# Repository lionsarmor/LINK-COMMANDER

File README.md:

# LINK COMMANDER — Rev D

**Buy the breadboard parts:** [Amazon checklist + ASINs](SHOPPING-AMAZON.md) · [Mouser checklist + SKUs](SHOPPING-MOUSER.md) · [Amazon order CSV](SHOPPING-AMAZON-ORDER.csv) · [Full Mouser CSV](SHOPPING-MOUSER-ORDER.csv) · [Keyboard-only Mouser CSV](SHOPPING-MOUSER-KEYBOARD.csv). Choose one checklist; do not buy both. Each covers the build and explicitly identifies outside-store exceptions. Skip parts already owned.

**Five finished PCB builds:** [Full Mouser PO (PDF)](MOUSER-PO-01-FIVE-PCBS.pdf) · [Full PO CSV](MOUSER-PO-01-FIVE-PCBS.csv) · [Chips-only PO (PDF)](MOUSER-PO-02-CHIPS-ONLY.pdf) · [Chips-only CSV](MOUSER-PO-02-CHIPS-ONLY.csv). Plain supplier parts tables; not submitted. Full order needs five modules and five fabricated PCBs supplied separately.

A through-hole USB keyboard and mouse adapter for the **Commander X16**.
The RP2040-Zero translates supported wired devices or 2.4 GHz USB receivers
into PS/2 keyboard and mouse signals. Rev D removes all gamepad support.

**Two USB inputs. Two PCB-mounted 7-pin DIN outputs. Two socketed DIP chips.**
The RP2040-Zero plugs into removable headers; every other carrier part is
through-hole. No USB hub or onboard radio is required.

A separate regulated **5 V / 2 A supply** powers the module and USB ports.
The X16 PS/2 +5 V lines supply only their signal pull-ups.

**Start breadboarding:** [Wiring instructions and parts list](BREADBOARD.md) ·
[Parts CSV](BREADBOARD-PARTS.csv) · [Complete wiring CSV](BREADBOARD-WIRING.csv)

- [Exploratory PS/2 simulation and its limits](hardware/rev-d/simulation/README.md)
- [Test points and expected readings](hardware/rev-d/test-points.md)
- [Student guide: how it works](hardware/rev-d/student-guide.md)
- [One-page schematic PDF](hardware/rev-d/review/schematic.pdf)
- [Assembly PDF](hardware/rev-d/review/assembly.pdf)
- [Editable KiCad project](hardware/rev-d/kicad/link-commander.kicad_pro)
- [Complete Rev D review ZIP](hardware/link-commander-rev-d-review.zip)
- [Breadboard guide and custom cables](BREADBOARD.md)
- [Pin-by-pin wiring table](hardware/rev-d/breadboard-wiring.csv)
- [Grouped BOM](hardware/rev-d/bom-grouped.csv) and [purchasing notes](hardware/rev-d/parts.md)
- [Design details and validation status](hardware/rev-d/README.md)
- [Firmware requirements](hardware/rev-d/firmware-contract.md)

The rounded **140 × 80 mm, two-layer PCB** retains 50 electrical parts
and four mounting holes, and now adds **26 labeled through-hole test pads**.
The student schematic shows seven circuit sections plus a test-point section,
physical pin numbers and connected wires.

**Engineering prototype:** CAD checks pass, but firmware, physical fit,
receiver compatibility and electrical operation still require testing.
No working bridge firmware or fabrication release is included yet. Start
with the standalone keyboard breadboard before connecting the X16.

Rev D uses **non-inverted PS/2 sense signals** and new component reference
numbers. Use only its wiring tables. Remove JP1 before connecting the
module's USB-C to a computer.

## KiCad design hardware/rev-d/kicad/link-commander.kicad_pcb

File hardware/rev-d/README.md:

# LINK COMMANDER — Rev D

Rev D translates supported **USB keyboards and mice** into the PS/2
keyboard and mouse interfaces used by the Commander X16. Wired peripherals
and manufacturers' 2.4 GHz USB receivers use the same two USB input ports.
Gamepad support has been removed from this revision.

The RP2040-Zero plugs into removable headers. Every other carrier component
is through-hole. There are **two socketed DIP chips and four transistors**.
The board is **140 × 80 mm**, has **two copper layers** and 4 mm corner radii,
and retains the KiCad/open-hardware logos.

The board and USB receivers use a separate regulated **5 V / 2 A supply**.
The X16 PS/2 +5 V pins supply only their signal pull-ups; they do not power
the RP2040 or USB ports. All grounds are shared.

## Start here

- [Exploratory PS/2 simulation and its limits](simulation/README.md)
- [Test-point map and expected readings](test-points.md) and [probe CSV](test-points.csv)
- [Student design guide: how the circuit works](student-guide.md)
- [One-page schematic PDF](review/schematic.pdf)
- [Assembly PDF](review/assembly.pdf) and [PCB preview](review/pcb-top.png)
- [Editable KiCad project](kicad/link-commander.kicad_pro)
- [Breadboard guide and custom cable table](breadboard.md)
- [Every physical pin](breadboard-wiring.csv) and [connections grouped by net](net-connections.csv)
- [Grouped BOM](bom-grouped.csv), [individual BOM](bom.csv), [purchasing notes](parts.md)
- [Firmware interface and test requirements](firmware-contract.md)
- [Validation reports](review/design-checks.txt), [PCB DRC](review/pcb-drc.txt)
- [Rebuild instructions](tools/README.md)

## What changed from Rev C

| | Rev C | Rev D |
|---|---:|---:|
| USB inputs | 4 | 2: keyboard and mouse |
| DIN outputs | 4 | 2: PS/2 keyboard and mouse |
| Socketed DIP ICs | 17 | 2 |
| Transistors | 7 | 4 |
| Circuit parts plus mounting holes | 143 | 54 |
| Additional bare test holes | — | 26 |
| Board | 230 × 130 mm, four layers | 140 × 80 mm, two layers |

The gamepad shift registers, resistor networks and control gates are gone.
One TPS2042P replaces the two individual USB power chips. One CD4050 handles all four PS/2 sense lines. The separate HC14 inverter
stage and four input/output series-resistor pairs have been removed. Both
channels of the USB power chip are enabled directly by ground, so no shared enable
transistor or RUN_ENABLE GPIO is required. Port fault LEDs remain useful
for students during bring-up.

**Rev D sense signals are non-inverting:** HIGH means the cable line is
HIGH. The old Rev C firmware assumptions and component reference numbers
must not be reused without updating them. PS/2 drive HIGH still pulls LOW.

The DIN-to-PS/2 cable signal assignment is unchanged, but the output
connectors are now J4 and J5. Use the Rev D wiring tables exclusively.

## Test access

TP1–TP26 add 26 bare plated holes: eight power rails, twelve PS/2
drive/cable/sense nodes, two USB fault outputs and four grounds. The board
now has 80 CAD positions: 50 electrical parts, four mounting holes and
26 optional test contacts. It still needs only two socketed chips.
USB data probing uses existing resistor pads to avoid added test branches.

## Prototype status

The saved PCB passes KiCad clearance/connectivity checks, and the exported
schematic netlist matches the canonical circuit. All populated component
pads are through-hole. These are CAD checks, not evidence of a working
physical adapter: module/socket fit, USB signal integrity, power sequencing,
PS/2 timing, firmware and receiver compatibility still need bench testing.
The two-layer ground pour is interrupted by routes; it is not a dedicated
unbroken reference plane or a controlled-impedance qualification.

No working bridge firmware or fabrication release is supplied here. Start
with the standalone breadboard tests. Do not connect the X16 until the
firmware and cable checks in the guide have passed.

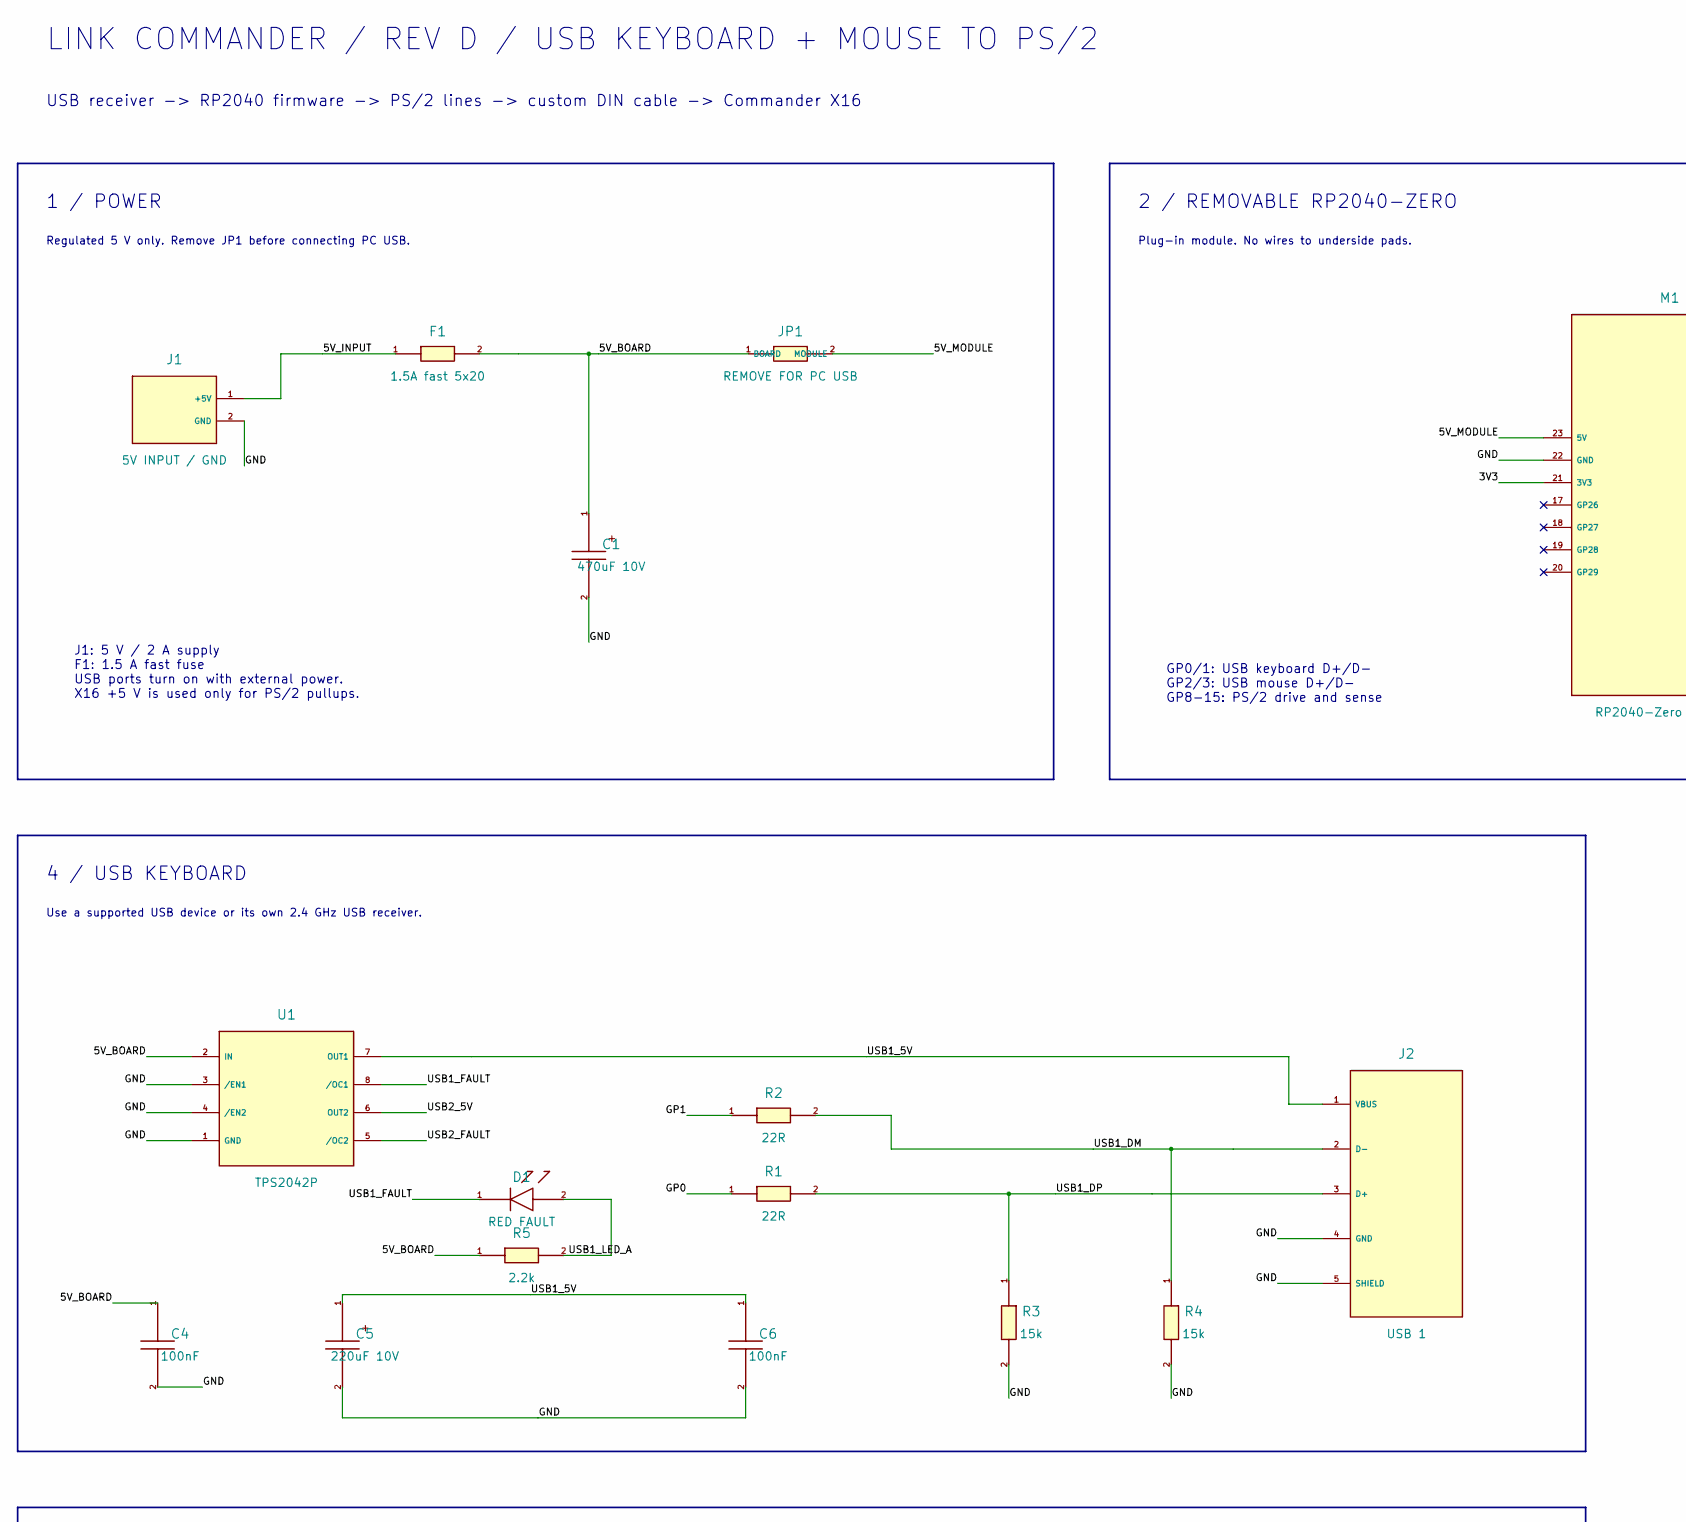
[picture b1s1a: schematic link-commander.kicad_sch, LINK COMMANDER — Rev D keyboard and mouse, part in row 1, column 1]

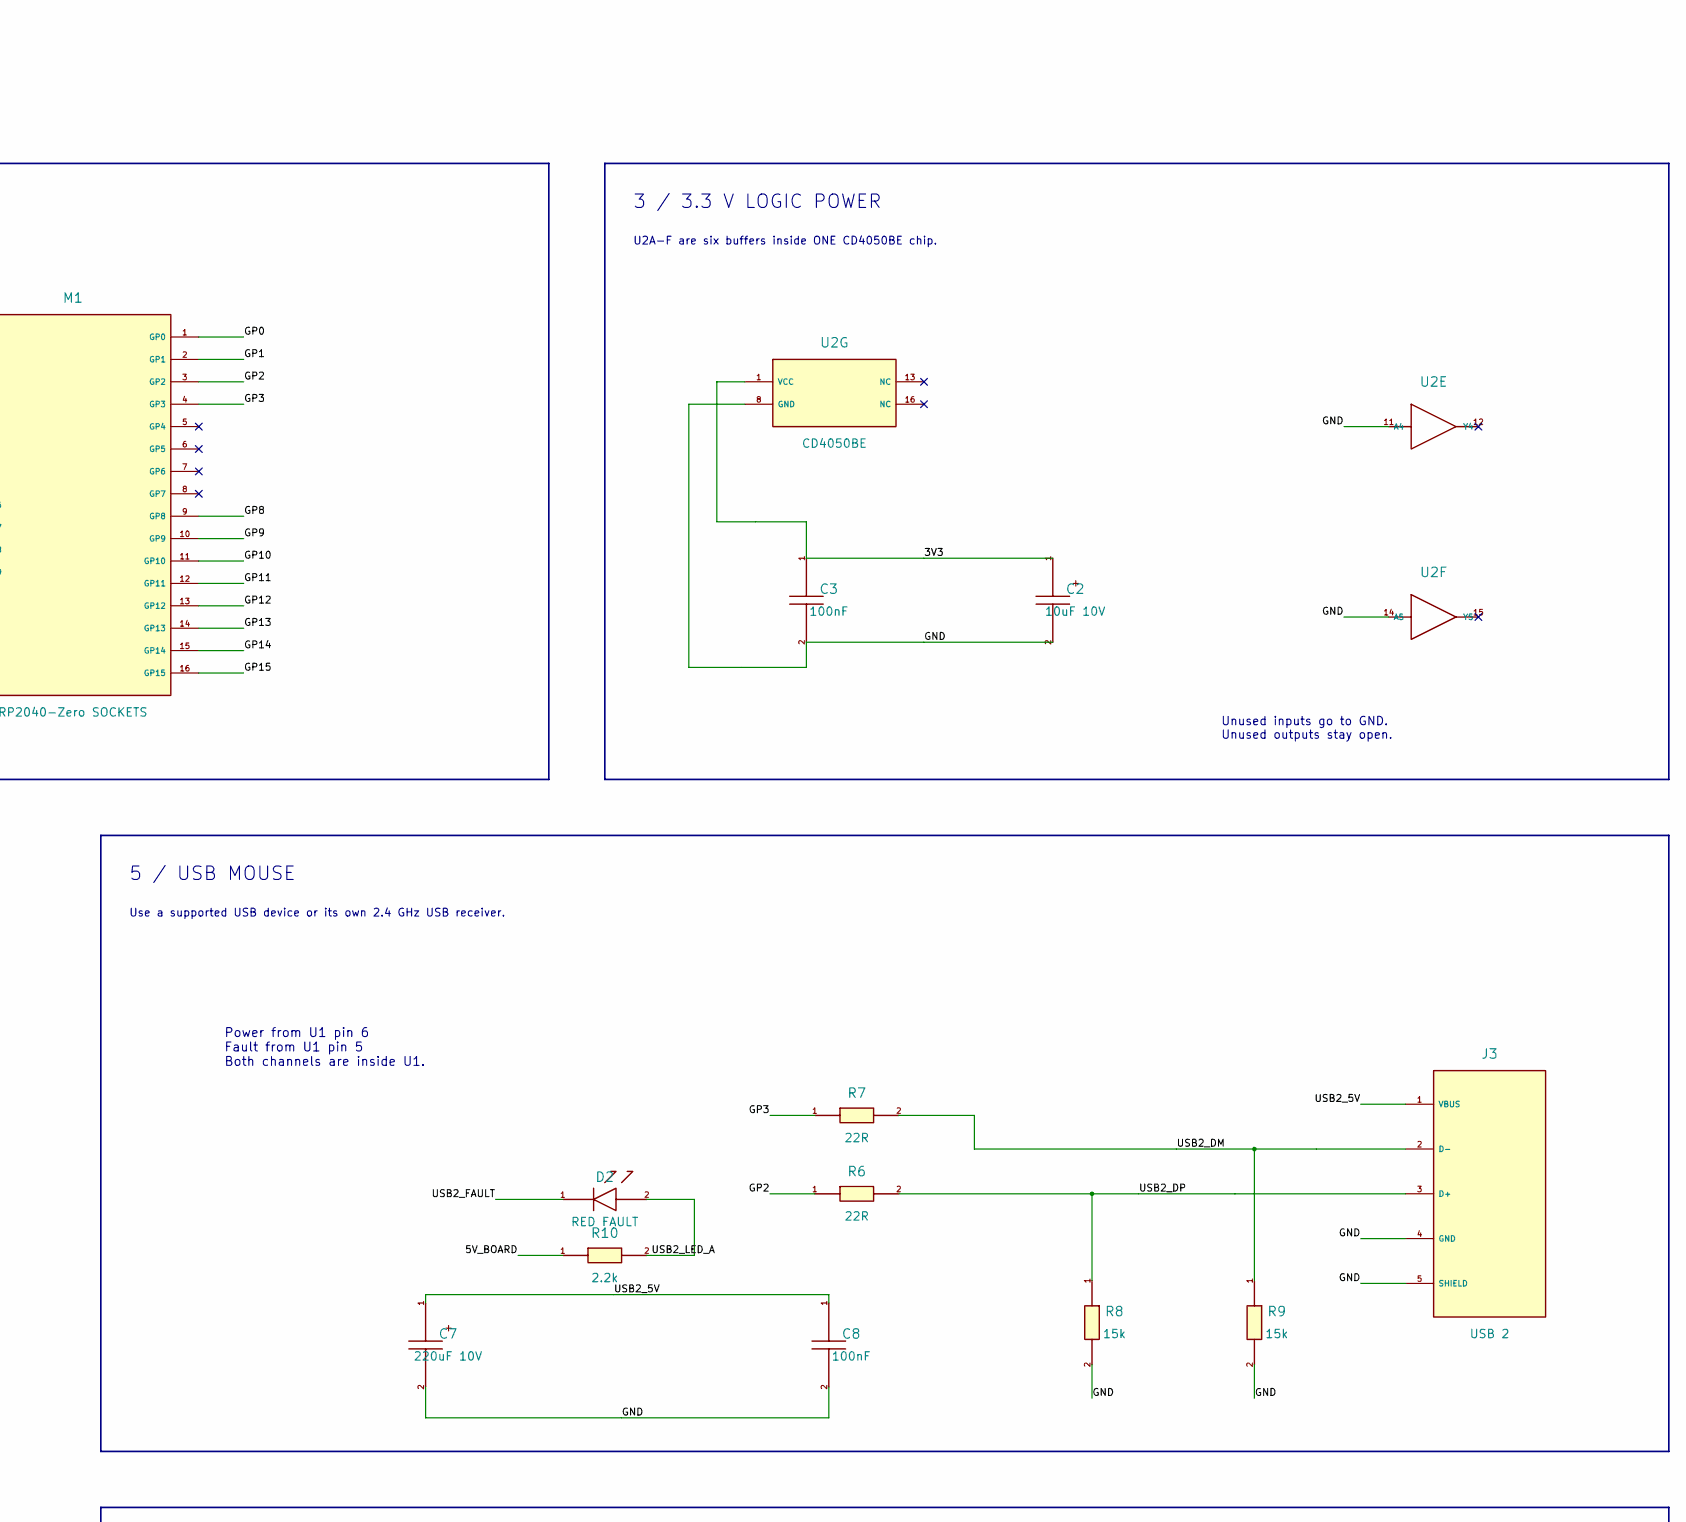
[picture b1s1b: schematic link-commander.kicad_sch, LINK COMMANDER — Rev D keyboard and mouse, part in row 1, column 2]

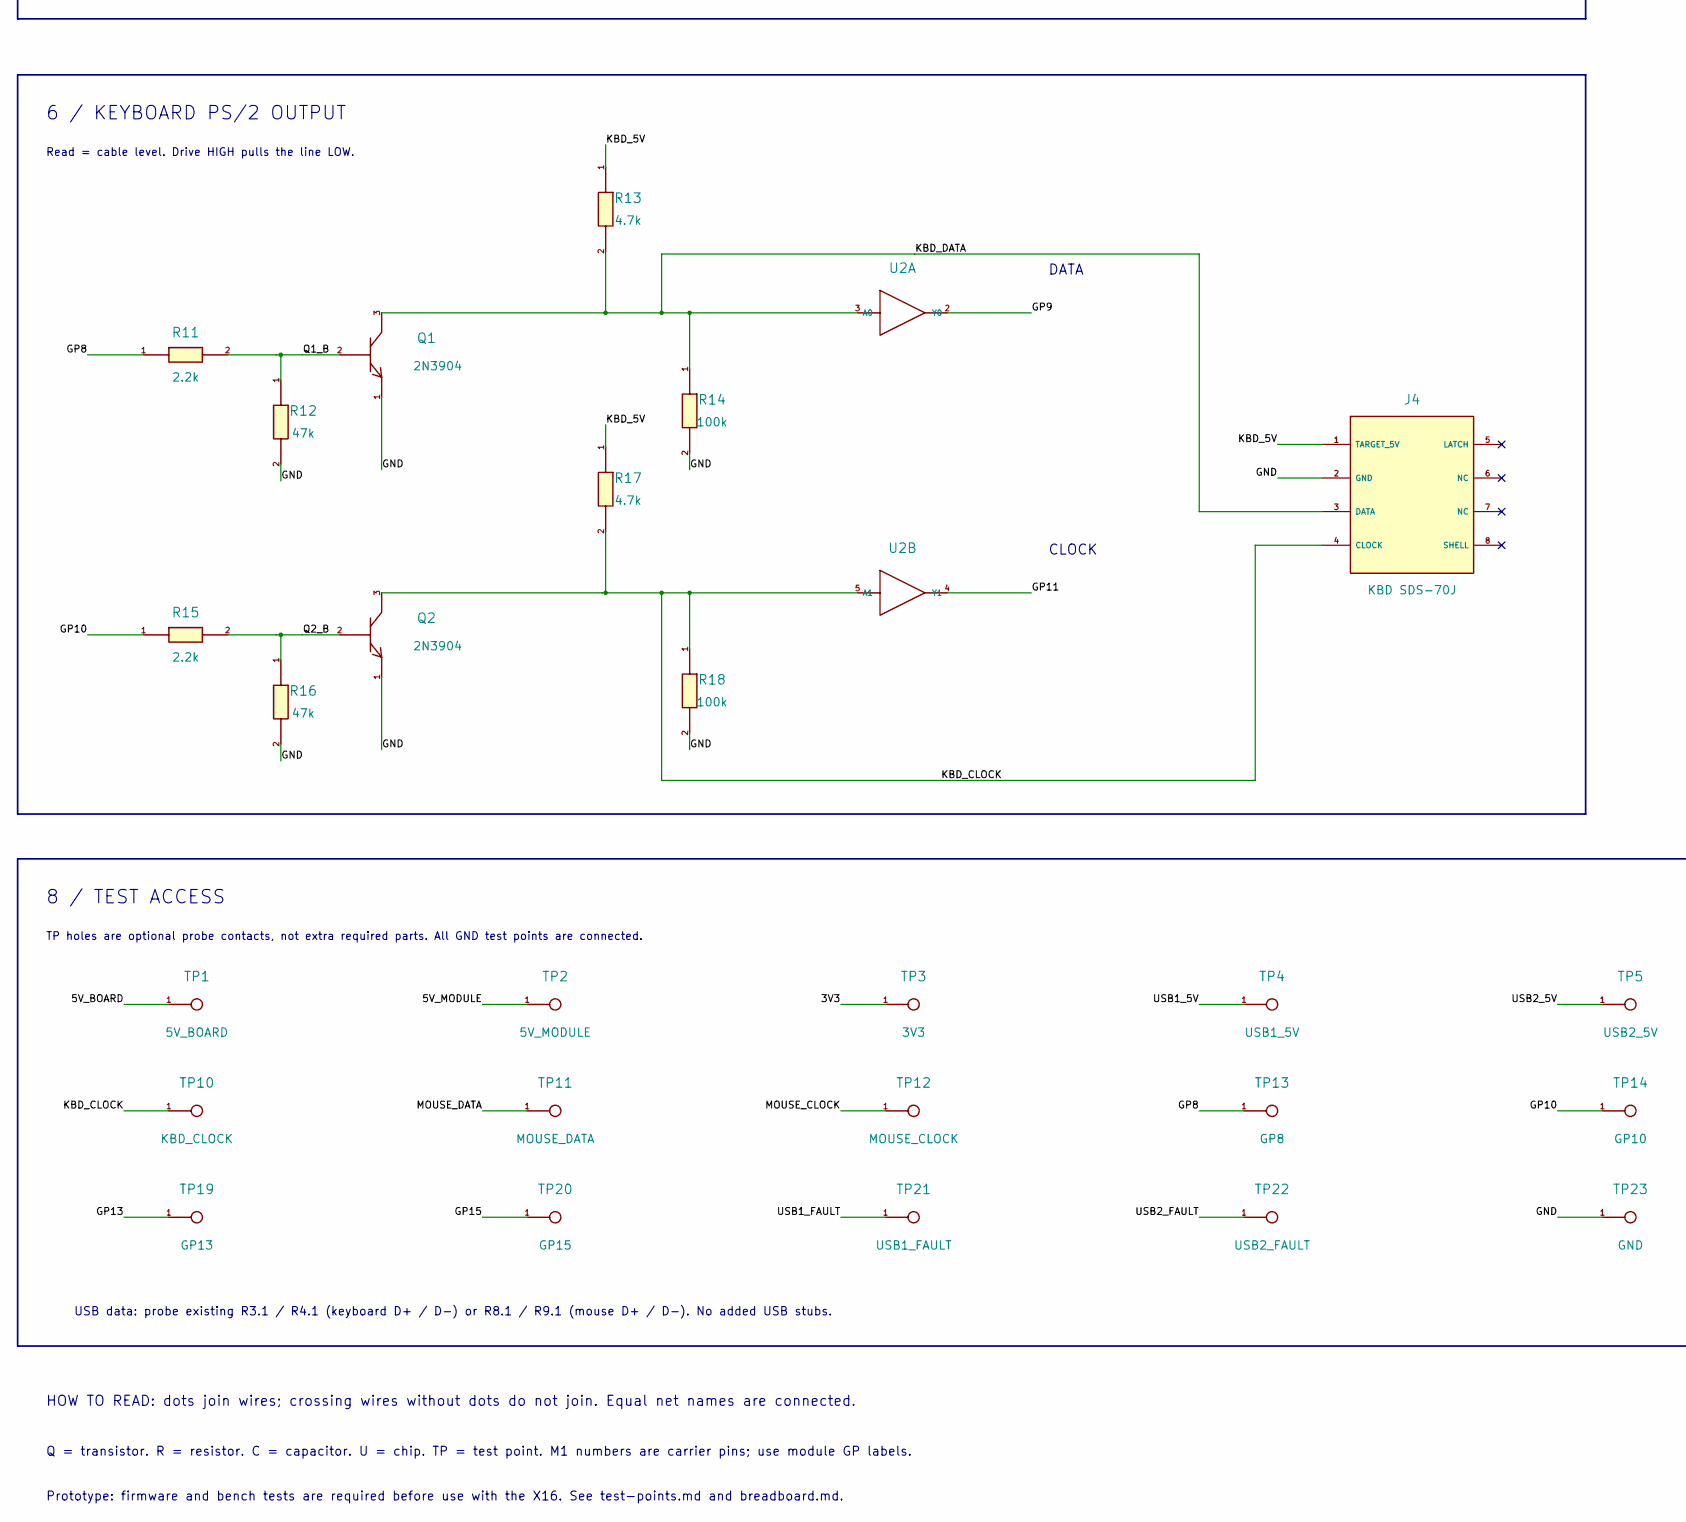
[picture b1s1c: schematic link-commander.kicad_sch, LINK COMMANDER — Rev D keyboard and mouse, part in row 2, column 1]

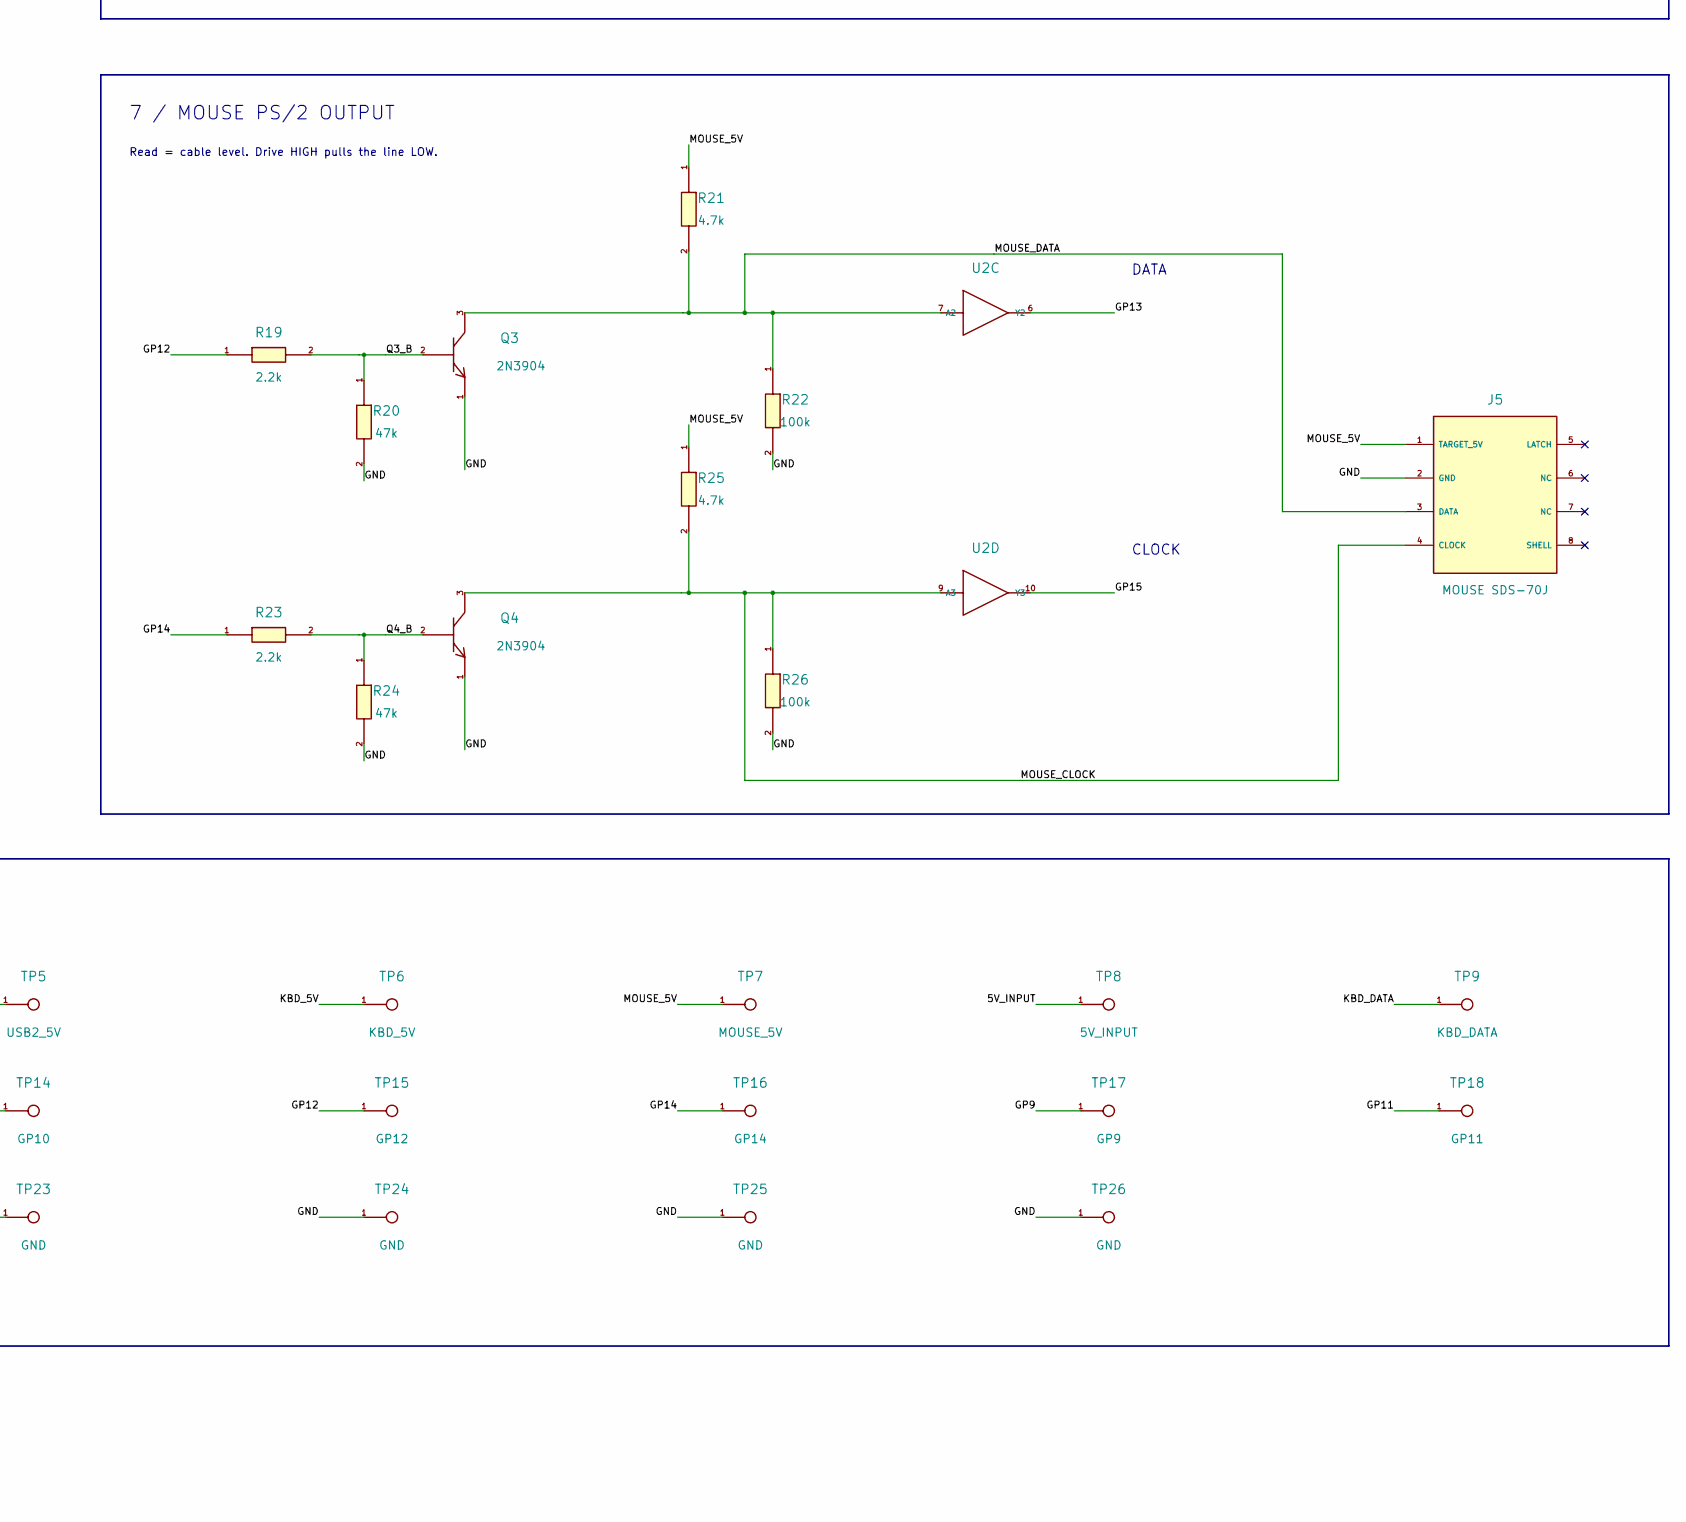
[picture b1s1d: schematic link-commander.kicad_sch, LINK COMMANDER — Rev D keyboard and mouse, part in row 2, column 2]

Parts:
C1: 470uF 10V; CP_Radial_D10.0mm_P5.00mm
C2: 10uF 10V; CP_Radial_D5.0mm_P2.00mm
C3, C4, C6, C8: 100nF; C_Disc_D5.0mm_W2.5mm_P5.00mm
C5, C7: 220uF 10V; CP_Radial_D6.3mm_P2.50mm
D1, D2: RED FAULT; LED_D3.0mm
F1: 1.5A fast 5x20; Fuseholder_Clip-5x20mm_Littelfuse_111_Lateral_P18.80x5.00mm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
J1: 5V INPUT / GND; TerminalBlock_TE_282834-2_1x02_P2.54mm_Horizontal
J2: USB 1; USB_A_Molex_67643_Horizontal
J3: USB 2; USB_A_Molex_67643_Horizontal
J4: KBD SDS-70J; SDS-70J
J5: MOUSE SDS-70J; SDS-70J
JP1: REMOVE FOR PC USB; PinHeader_1x02_P2.54mm_Vertical
M1: RP2040-Zero SOCKETS; RP2040_Zero_HeaderOnly
Q1, Q2, Q3, Q4: 2N3904; TO-92_Inline_Wide
R1, R2, R6, R7: 22R; R_Axial_DIN0207_L6.3mm_D2.5mm_P10.16mm_Horizontal
R3, R4, R8, R9: 15k; R_Axial_DIN0207_L6.3mm_D2.5mm_P10.16mm_Horizontal
R5, R10, R11, R15, R19, R23: 2.2k; R_Axial_DIN0207_L6.3mm_D2.5mm_P10.16mm_Horizontal
R12, R16, R20, R24: 47k; R_Axial_DIN0207_L6.3mm_D2.5mm_P10.16mm_Horizontal
R13, R17, R21, R25: 4.7k; R_Axial_DIN0207_L6.3mm_D2.5mm_P10.16mm_Horizontal
R14, R18, R22, R26: 100k; R_Axial_DIN0207_L6.3mm_D2.5mm_P10.16mm_Horizontal
TP1: 5V_BOARD; TestPoint_THT_1mm
TP2: 5V_MODULE; TestPoint_THT_1mm
TP3: 3V3; TestPoint_THT_1mm
TP4: USB1_5V; TestPoint_THT_1mm
TP5: USB2_5V; TestPoint_THT_1mm
TP6: KBD_5V; TestPoint_THT_1mm
TP7: MOUSE_5V; TestPoint_THT_1mm
TP8: 5V_INPUT; TestPoint_THT_1mm
TP9: KBD_DATA; TestPoint_THT_1mm
TP10: KBD_CLOCK; TestPoint_THT_1mm
TP11: MOUSE_DATA; TestPoint_THT_1mm
TP12: MOUSE_CLOCK; TestPoint_THT_1mm
TP13: GP8; TestPoint_THT_1mm
TP14: GP10; TestPoint_THT_1mm
TP15: GP12; TestPoint_THT_1mm
TP16: GP14; TestPoint_THT_1mm
TP17: GP9; TestPoint_THT_1mm
TP18: GP11; TestPoint_THT_1mm
TP19: GP13; TestPoint_THT_1mm
TP20: GP15; TestPoint_THT_1mm
TP21: USB1_FAULT; TestPoint_THT_1mm
TP22: USB2_FAULT; TestPoint_THT_1mm
TP23, TP24, TP25, TP26: GND; TestPoint_THT_1mm
U1: TPS2042P; DIP-8_W7.62mm_Socket
U2: CD4050BE; DIP-16_W7.62mm_Socket

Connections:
3V3: C2.1, C3.1, M1.21 (3V3), TP3.1, U2.1 (VCC)
5V_BOARD: C1.1, C4.1, F1.2 (OUT), JP1.1 (BOARD), R5.1, R10.1, TP1.1, U1.2 (IN)
5V_INPUT: F1.1 (IN), J1.1 (+5V), TP8.1
5V_MODULE: JP1.2 (MODULE), M1.23 (5V), TP2.1
GND: C1.2, C2.2, C3.2, C4.2, C5.2, C6.2, C7.2, C8.2, J1.2 (GND), J2.4 (GND), J2.5 (SHIELD), J3.4 (GND), J3.5 (SHIELD), J4.2 (GND), J5.2 (GND), M1.22 (GND), Q1.1 (E), Q2.1 (E), Q3.1 (E), Q4.1 (E), R3.2, R4.2, R8.2, R9.2, R12.2, R14.2, R16.2, R18.2, R20.2, R22.2, R24.2, R26.2, TP23.1, TP24.1, TP25.1, TP26.1, U1.1 (GND), U1.3 (/EN1), U1.4 (/EN2), U2.8 (GND), U2.11 (A4), U2.14 (A5)
GP0: M1.1 (GP0), R1.1
GP1: M1.2 (GP1), R2.1
GP2: M1.3 (GP2), R6.1
GP3: M1.4 (GP3), R7.1
GP8: M1.9 (GP8), R11.1, TP13.1
GP9: M1.10 (GP9), TP17.1, U2.2 (Y0)
GP10: M1.11 (GP10), R15.1, TP14.1
GP11: M1.12 (GP11), TP18.1, U2.4 (Y1)
GP12: M1.13 (GP12), R19.1, TP15.1
GP13: M1.14 (GP13), TP19.1, U2.6 (Y2)
GP14: M1.15 (GP14), R23.1, TP16.1
GP15: M1.16 (GP15), TP20.1, U2.10 (Y3)
KBD_5V: J4.1 (TARGET_5V), R13.1, R17.1, TP6.1
KBD_CLOCK: J4.4 (CLOCK), Q2.3 (C), R17.2, R18.1, TP10.1, U2.5 (A1)
KBD_DATA: J4.3 (DATA), Q1.3 (C), R13.2, R14.1, TP9.1, U2.3 (A0)
MOUSE_5V: J5.1 (TARGET_5V), R21.1, R25.1, TP7.1
MOUSE_CLOCK: J5.4 (CLOCK), Q4.3 (C), R25.2, R26.1, TP12.1, U2.9 (A3)
MOUSE_DATA: J5.3 (DATA), Q3.3 (C), R21.2, R22.1, TP11.1, U2.7 (A2)
Q1_B: Q1.2 (B), R11.2, R12.1
Q2_B: Q2.2 (B), R15.2, R16.1
Q3_B: Q3.2 (B), R19.2, R20.1
Q4_B: Q4.2 (B), R23.2, R24.1
USB1_5V: C5.1, C6.1, J2.1 (VBUS), TP4.1, U1.7 (OUT1)
USB1_DM: J2.2 (D-), R2.2, R4.1
USB1_DP: J2.3 (D+), R1.2, R3.1
USB1_FAULT: D1.1 (K), TP21.1, U1.8 (/OC1)
USB1_LED_A: D1.2 (A), R5.2
USB2_5V: C7.1, C8.1, J3.1 (VBUS), TP5.1, U1.6 (OUT2)
USB2_DM: J3.2 (D-), R7.2, R9.1
USB2_DP: J3.3 (D+), R6.2, R8.1
USB2_FAULT: D2.1 (K), TP22.1, U1.5 (/OC2)
USB2_LED_A: D2.2 (A), R10.2

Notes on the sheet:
LINK COMMANDER / REV D / USB KEYBOARD + MOUSE TO PS/2
USB receiver -> RP2040 firmware -> PS/2 lines -> custom DIN cable -> Commander X16
1 / POWER
Regulated 5 V only. Remove JP1 before connecting PC USB.
J1: 5 V / 2 A supply F1: 1.5 A fast fuse USB ports turn on with external power. X16 +5 V is used only for PS/2 pullups.
2 / REMOVABLE RP2040-ZERO
Plug-in module. No wires to underside pads.
GP0/1: USB keyboard D+/D- GP2/3: USB mouse D+/D- GP8-15: PS/2 drive and sense
3 / 3.3 V LOGIC POWER
U2A-F are six buffers inside ONE CD4050BE chip.
Unused inputs go to GND. Unused outputs stay open.
4 / USB KEYBOARD
Use a supported USB device or its own 2.4 GHz USB receiver.
5 / USB MOUSE
Power from U1 pin 6 Fault from U1 pin 5 Both channels are inside U1.
6 / KEYBOARD PS/2 OUTPUT
Read = cable level. Drive HIGH pulls the line LOW.
DATA
CLOCK
7 / MOUSE PS/2 OUTPUT
8 / TEST ACCESS
TP holes are optional probe contacts, not extra required parts. All GND test points are connected.
USB data: probe existing R3.1 / R4.1 (keyboard D+ / D-) or R8.1 / R9.1 (mouse D+ / D-). No added USB stubs.
HOW TO READ: dots join wires; crossing wires without dots do not join. Equal net names are connected.
Q = transistor. R = resistor. C = capacitor. U = chip. TP = test point. M1 numbers are carrier pins; use module GP labels.
Prototype: firmware and bench tests are required before use with the X16. See test-points.md and breadboard.md.

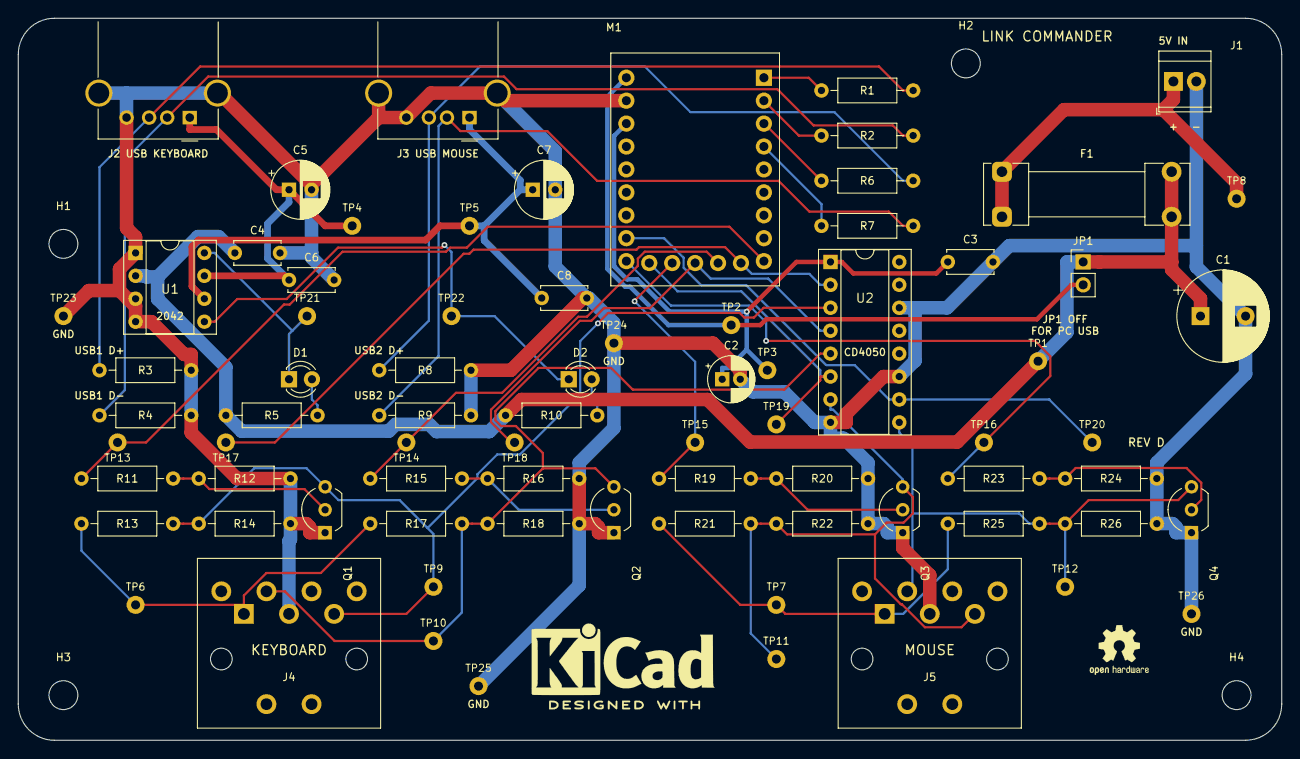
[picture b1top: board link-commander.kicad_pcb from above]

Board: 2 copper layers, 140.0 x 80.0 mm, 82 parts (0 on the bottom side), 37 nets.

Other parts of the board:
H1, H2, H3, H4: M3; MountingHole_3.2mm_M3
LOGO1: KiCad-Logo2_8mm_SilkScreen
LOGO2: OSHW-Logo2_7.3x6mm_SilkScreen

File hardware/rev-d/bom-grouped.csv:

Quantity,Part / value,Through-hole footprint,References
1,5V INPUT / GND,TerminalBlock_TE_282834-2_1x02_P2.54mm_Horizontal,J1
1,1.5A fast 5x20,Fuseholder_Clip-5x20mm_Littelfuse_111_Lateral_P18.80x5.00mm_D1.17mm_Horizontal,F1
1,REMOVE FOR PC USB,PinHeader_1x02_P2.54mm_Vertical,JP1
1,RP2040-Zero SOCKETS,RP2040_Zero_HeaderOnly,M1
1,470uF 10V,CP_Radial_D10.0mm_P5.00mm,C1
1,10uF 10V,CP_Radial_D5.0mm_P2.00mm,C2
4,100nF,C_Disc_D5.0mm_W2.5mm_P5.00mm,C3 C4 C6 C8
1,USB 1,USB_A_Molex_67643_Horizontal,J2
1,TPS2042P,DIP-8_W7.62mm_Socket,U1
4,22R,R_Axial_DIN0207_L6.3mm_D2.5mm_P10.16mm_Horizontal,R1 R2 R6 R7
4,15k,R_Axial_DIN0207_L6.3mm_D2.5mm_P10.16mm_Horizontal,R3 R4 R8 R9
6,2.2k,R_Axial_DIN0207_L6.3mm_D2.5mm_P10.16mm_Horizontal,R5 R10 R11 R15 R19 R23
2,220uF 10V,CP_Radial_D6.3mm_P2.50mm,C5 C7
2,RED FAULT,LED_D3.0mm,D1 D2
1,USB 2,USB_A_Molex_67643_Horizontal,J3
1,KBD SDS-70J,SDS-70J,J4
1,MOUSE SDS-70J,SDS-70J,J5
4,2N3904,TO-92_Inline_Wide,Q1 Q2 Q3 Q4
4,47k,R_Axial_DIN0207_L6.3mm_D2.5mm_P10.16mm_Horizontal,R12 R16 R20 R24
4,4.7k,R_Axial_DIN0207_L6.3mm_D2.5mm_P10.16mm_Horizontal,R13 R17 R21 R25
4,100k,R_Axial_DIN0207_L6.3mm_D2.5mm_P10.16mm_Horizontal,R14 R18 R22 R26
1,CD4050BE,DIP-16_W7.62mm_Socket,U2
4,M3,MountingHole_3.2mm_M3,H1 H2 H3 H4
1,5V_BOARD,TestPoint_THT_1mm,TP1
1,5V_MODULE,TestPoint_THT_1mm,TP2
1,3V3,TestPoint_THT_1mm,TP3
1,USB1_5V,TestPoint_THT_1mm,TP4
1,USB2_5V,TestPoint_THT_1mm,TP5
1,KBD_5V,TestPoint_THT_1mm,TP6
1,MOUSE_5V,TestPoint_THT_1mm,TP7
1,5V_INPUT,TestPoint_THT_1mm,TP8
1,KBD_DATA,TestPoint_THT_1mm,TP9
1,KBD_CLOCK,TestPoint_THT_1mm,TP10
1,MOUSE_DATA,TestPoint_THT_1mm,TP11
1,MOUSE_CLOCK,TestPoint_THT_1mm,TP12
1,GP8,TestPoint_THT_1mm,TP13
1,GP10,TestPoint_THT_1mm,TP14
1,GP12,TestPoint_THT_1mm,TP15
1,GP14,TestPoint_THT_1mm,TP16
1,GP9,TestPoint_THT_1mm,TP17
1,GP11,TestPoint_THT_1mm,TP18
1,GP13,TestPoint_THT_1mm,TP19
1,GP15,TestPoint_THT_1mm,TP20
1,USB1_FAULT,TestPoint_THT_1mm,TP21
1,USB2_FAULT,TestPoint_THT_1mm,TP22
4,GND,TestPoint_THT_1mm,TP23 TP24 TP25 TP26

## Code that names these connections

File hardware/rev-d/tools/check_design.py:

"""Check the exported schematic and independent Rev D interface requirements."""
import json,csv,xml.etree.ElementTree as ET
from collections import defaultdict
from design import ROOT
parts=json.loads((ROOT/'circuit.json').read_text());by={p['ref']:p for p in parts}
expected=defaultdict(set)
for p in parts:
 for pin,(_,net) in p['pins'].items():
  if net:expected[net].add((p['ref'],pin))
actual={}
for net in ET.parse(ROOT/'review/schematic.xml').getroot().find('nets'):
 name=net.attrib['name'].removeprefix('/')
 if name.startswith('unconnected-'):continue
 actual[name]={(n.attrib['ref'],n.attrib['pin']) for n in net.findall('node')}
assert actual==dict(expected),'Exported schematic differs from canonical pin assignments'
assert len(by)==len(parts)
assert {p['value'] for p in parts if p['ref'].startswith('U')}=={'TPS2042P','CD4050BE'}
assert {p['ref'] for p in parts if p['ref'].startswith('U')}=={'U1','U2'}
assert not any('PAD' in n or 'CHAIN' in n or 'RUN_ENABLE' in n or 'OUTPUT_DISABLE' in n for n in expected)
assert set(by['M1']['pins'])=={str(i) for i in range(1,24)}
assert sum(net is not None for name,net in by['M1']['pins'].values())==15 # 12 GPIO + 3 supply pins
for pin in [5,6,7,8,17,18,19,20]:assert by['M1']['pins'][str(pin)][1] is None
for i in range(2):
 n=i+1;j=by[f'J{n+1}'];u=by['U1']
 assert j['pins']['2'][1]==f'USB{n}_DM' and j['pins']['3'][1]==f'USB{n}_DP'
 assert u['pins'][str(3+i)][1]=='GND' and u['value']=='TPS2042P'
 for k,suffix in [(0,'DP'),(1,'DM')]:
  assert any(p['value']=='22R' and {v[1] for v in p['pins'].values()}=={f'GP{2*i+k}',f'USB{n}_{suffix}'} for p in parts)
  assert any(p['value']=='15k' and {v[1] for v in p['pins'].values()}=={'GND',f'USB{n}_{suffix}'} for p in parts)
assert by['U1']['pins']['2'][1]=='5V_BOARD' and by['U1']['pins']['1'][1]=='GND'
for pin,net in [(7,'USB1_5V'),(6,'USB2_5V'),(8,'USB1_FAULT'),(5,'USB2_FAULT')]:assert by['U1']['pins'][str(pin)][1]==net
for i,(prefix,kind,inp,outp) in enumerate([('KBD','DATA',3,2),('KBD','CLOCK',5,4),('MOUSE','DATA',7,6),('MOUSE','CLOCK',9,10)]):
 line=f'{prefix}_{kind}';q=by[f'Q{i+1}'];r=11+4*i
 assert q['pins']=={'1':['E','GND'],'2':['B',f'Q{i+1}_B'],'3':['C',line]}
 assert by['U2']['pins'][str(inp)][1]==line
 assert by['U2']['pins'][str(outp)][1]==f'GP{9+2*i}' # non-inverted; no HC14
 assert {v[1] for v in by[f'R{r}']['pins'].values()}=={f'GP{8+2*i}',f'Q{i+1}_B'}
 assert {v[1] for v in by[f'R{r+2}']['pins'].values()}=={line,prefix+'_5V'}
 assert {v[1] for v in by[f'R{r+3}']['pins'].values()}=={line,'GND'}
assert by['U2']['pins']['1'][1]=='3V3' and by['U2']['pins']['8'][1]=='GND'
for p in [11,14]:assert by['U2']['pins'][str(p)][1]=='GND'
for p in [12,13,15,16]:assert by['U2']['pins'][str(p)][1] is None
for ref,prefix in [('J4','KBD'),('J5','MOUSE')]:
 assert [by[ref]['pins'][str(k)][1] for k in range(1,5)]==[prefix+'_5V','GND',prefix+'_DATA',prefix+'_CLOCK']
 assert all(by[ref]['pins'][str(k)][1] is None for k in range(5,9))
 assert all(r.startswith(('J','R','TP')) for r,pin in expected[prefix+'_5V'])
tps={p['ref']:p['pins']['1'][1] for p in parts if p['ref'].startswith('TP')}
assert len(tps)==26 and list(tps.values()).count('GND')==4
assert set(tps.values())=={'GND','5V_INPUT','5V_BOARD','5V_MODULE','3V3','USB1_5V','USB2_5V','KBD_5V','MOUSE_5V','USB1_FAULT','USB2_FAULT','KBD_DATA','KBD_CLOCK','MOUSE_DATA','MOUSE_CLOCK',*[f'GP{i}' for i in range(8,16)]}
rows=list(csv.DictReader((ROOT/'breadboard-wiring.csv').open()))
assert len(rows)==sum(len(p["pins"]) for p in parts)
for row in rows:
 pin=by[row['Component']]['pins'][row['Physical pin']]
 assert row['Pin name']==pin[0] and row['Connect to net']==(pin[1] or 'NO CONNECTION')
probe_rows=list(csv.DictReader((ROOT/'test-points.csv').open()))
assert len(probe_rows)==30
for row in probe_rows:
 ref,pin=row['Probe location'].split('.')
 assert by[ref]['pins'][pin][1]==row['Net']
for ref,net in [('R3','USB1_DP'),('R4','USB1_DM'),('R8','USB2_DP'),('R9','USB2_DM')]:assert by[ref]['pins']['1'][1]==net and by[ref]['pins']['2'][1]=='GND'
assert sum(int(r['Quantity']) for r in csv.DictReader((ROOT/'bom-grouped.csv').open()))==len(parts)
report=f'''PASS: {len(parts)} components including mounting holes; {len(expected)} named nets; {len(rows)} physical pin assignments.
PASS: 26 through-hole test contacts cover power, PS/2, USB faults and four ground locations.
PASS: exported schematic netlist exactly matches the canonical circuit.
PASS: only two USB inputs, two PS/2 DIN outputs; no gamepad circuitry or nets.
PASS: two DIP chips; header-only RP2040 with 12 used GPIOs and 8 unused GPIOs.
PASS: dual TPS2042P outputs/faults and both active-low enables are correct.
PASS: four USB 22-ohm series paths and four 15-kilohm host pulldowns.
PASS: four low-only transistor outputs and four non-inverting CD4050 sense paths.
PASS: CD4050 supply/unused pins and target-reference power separation.
NOT TESTED: physical fit, electrical timing/thresholds, USB signal integrity,
firmware operation, USB receiver compatibility, or actual X16 operation.
This is a netlist/structural check, not an electrical simulation or full ERC.
'''
(ROOT/'review/design-checks.txt').write_text(report);print(report)
